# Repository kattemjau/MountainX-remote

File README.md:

# MountainX-remote
PCB of remote, designed in Kicad
Inspired by Adafruit, and SolidGeek

https://learn.adafruit.com/bluefruit-nrf52-feather-learning-guide?view=all#downloads

https://www.electric-skateboard.builders/t/simple-3d-printed-nrf-remote-arduino-controlled/28543

V3 is not yet tested

Arduino compadible CODE can be found here:
https://github.com/Heplaphon/MountainX-Remote

Follow setupguide from Adafruit: https://learn.adafruit.com/bluefruit-nrf52-feather-learning-guide?view=all#arduino-bsp-setup

V2 up and working with Arduino IDE, can be programmed over USB, JTAG and OTA (bluetooth)

3D model of PCB can be found here:
https://github.com/kattemjau/MountainX-remote/tree/master/3D%20model

3D model of remote can be found here:
https://github.com/kattemjau/MountainX-remote/tree/master/3D%20model/V2

Images can be found here:
https://github.com/kattemjau/MountainX-remote/tree/master/Images

Features:

3 Hall sensors for more accurate readings, 
Nordic NRF52 Bluetooth 5, Arm Cotex m4,
Oled screen with telematry from Vesc: Speed, distance, battery voltage, error codes e.t.c, 
Remote battery reading, 
1A Fast charger, 
Long battery life, 
Dual battery to prevent battery disconnect due to shaking, 
Spring loaded knob and trigger, 
Deadmans switch, 
Opensource reprogrammable firmware with arduino IDE, 
Connects with up to 20 clients, long range and high bandwidth,

Changes:

3D model now available, 
Integrated OLED screen, 
Correct angles on Hall sensors, 
Extra battery plug, 
More leds, 
More decoupling caps, 
Better layout, 
Changes to footprints, 
NOW USB C, 

Note:
Jtag programming header is mirrored, just flip the cable to get it to work. "Jtag is not needed"
https://shop-us.segger.com/J_Link_EDU_mini_p/8.08.91.htm

Footprint for Raytac NRF52832 not correct, and SS12D11 (SWITCH) is missing

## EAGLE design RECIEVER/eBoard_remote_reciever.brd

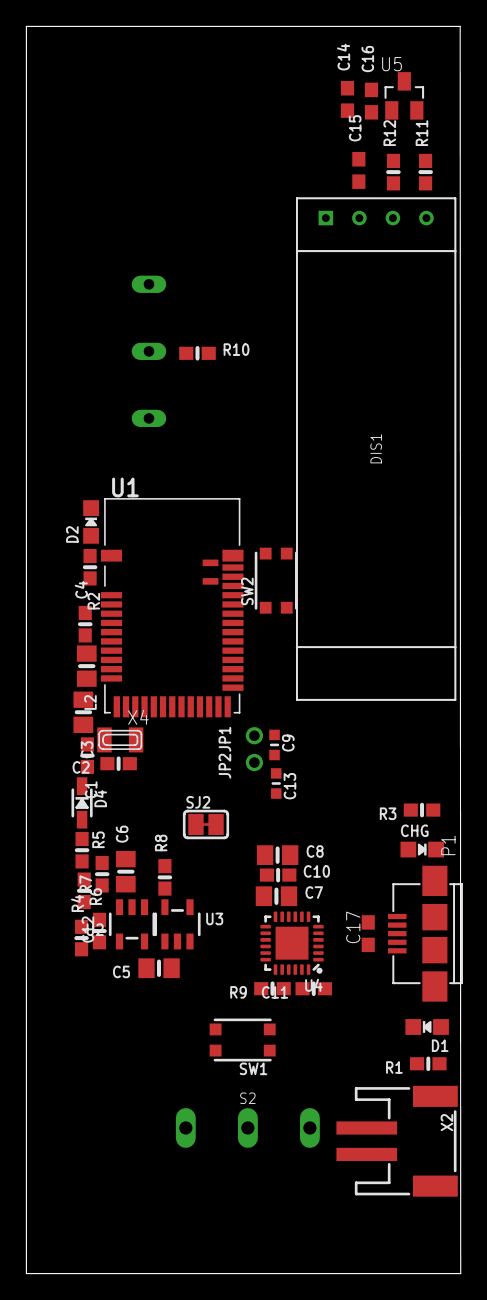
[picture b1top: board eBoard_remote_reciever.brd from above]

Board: 2 copper layers, 32.9 x 94.5 mm, 50 parts (1 on the bottom side), 33 nets, no tracks yet.

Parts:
C1, C2: 22pF; 0603-NO
C3: 10uF; 0805-NO
C4: 1uF; 0603-NO
C5, C6, C8: 10µF; 0805-NO
C7: 10uf; 0805-NO
C9, C13: 300pF; _0603MP
C10, C11: 0.1uF; 0603-NO
C12: 1nF; 0603-NO
C14, C15, C17: 10µF; C0603
C16: 100n; C0603
CHG: ORANGE; CHIPLED_0805_NOOUTLINE
D1: RED; CHIPLED_0805_NOOUTLINE
D2: BLUE; CHIPLED_0805_NOOUTLINE
D4: 1N4148; SOD-323
DIS1: OLED
JP1, JP2: 1X01_2MM
L2: 10uH; 0805-NO
P1: USB; USB-MICRO-B
R1, R2, R3, R9, R10: 1K; 0603-NO
R4: 806K; 0603-NO
R5: 100K; 0603-NO
R6: 2M; 0603-NO
R7, R8: 10K; 0603-NO
R11, R12: 2k2; 0603-NO
S1: K9-1267B-L
S2: SS12D11
SJ2: BAT; SOLDERJUMPER_CLOSEDWIRE
SW1, SW2: KMR2; BTN_KMR2_4.6X2.8
U1: MDBT42; BLE_MODULE_RAYTAC_MDBT42
U2: AP2112(3.3V); SOT23-5
U3: MCP73831T-2ACI/OT; SOT23-5
U4: CP2104; QFN24_4MM_SMSC
U5: SOT23
X2: JSTPH; JSTPH2
X4: 32.768; XTAL3215

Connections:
3.3V: C3.1, C8.1, C10.1, C14.1, C15.1, C16.1, D4.C, DIS1.VCC, R7.2, R10.2, R11.2, R12.2, U1.11, U2.5, U4.5, U4.6, U4.7, U5.1
A7/P0.31: C12.1, R4.2, R6.1, U1.8
DFU: SW2.B, SW2.B', U1.34
DTR: C11.2, U4.23
EN: R5.1, U2.3
GND: C1.2, C2.2, C3.2, C4.2, C5.2, C6.2, C7.2, C8.2, C9.2, C10.2, C12.2, C13.2, C14.2, C15.2, C16.2, C17.2, D1.C, D2.C, DIS1.GND, P1.5, P1.G1, P1.G2, P1.G3, P1.G4, R6.2, R8.2, S1.P1, SW1.B, SW1.B', SW2.A, SW2.A', U1.1, U1.12, U1.24, U1.39, U2.2, U3.2, U4.2, U4.THERM, U5.3, X2.1
LED1: R1.2, U1.31
LED2: R2.2, U1.33
unnamed: C1.1, U1.13, X4.P$1
unnamed: C2.1, U1.14, X4.P$2
unnamed: L2.2, U1.10
unnamed: CHG.C, R3.1
unnamed: D1.A, R1.1
unnamed: D2.A, R2.1
unnamed: C4.1, L2.1, U1.9
unnamed: R3.2, U3.1
unnamed: R8.1, U3.5
unnamed: R9.1, U4.21
unnamed: C11.1, SJ2.2
unnamed: C7.1, U4.16
P0.07: R10.1, S1.P2, U1.20
P0.09/NFC1: C13.1, JP2.1, U1.22
P0.10/NFC2: C9.1, JP1.1, U1.23
RESET: D4.A, R7.1, SJ2.1, SW1.A, SW1.A', U1.35
RXD: R9.2, U1.21
SCL: DIS1.SCL, R12.1, U1.3
SDA: DIS1.SDA, R11.1, U1.2
TXD: U1.19, U4.20
USBD+: P1.3, U4.3
USBD-: P1.2, U4.4
VBAT: C6.1, R4.1, R5.2, S2.2, U2.1, X2.2
VBAT_PRESWITCH: C5.1, S2.1, U3.3
VBUS: C17.1, CHG.A, P1.1, U3.4, U4.8

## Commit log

2019-01-08 V2 update
2019-04-18 V2.1
2019-04-23 this
2019-04-23 added dual jst and 3d models
2019-04-23 oled schem
2019-04-24 started Layout V3
2019-04-24 added rgb led V3
2019-04-27 updated 3d modelis
2019-04-29 Added 3D models
2019-04-29 more pics
2019-04-30 Create LICENSE

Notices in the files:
parts and their libraries:
microbuilder: This work is placed in the public domain, and may be freely used for commercial and non-commercial work with the following conditions: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
